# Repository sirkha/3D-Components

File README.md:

3D Components
=============

These are various components and assemblies that I have modeled for use 
in designing 3D printed objects.

I hope you can find some of them as useful as I have.

License
-------
[CC-BY-SA][7]

Attribution
-----------
Thanks to [Adafruit][1] and [Arduino][2] for putting their pcb files on the 
web, which makes the assemblies possible. Also, thanks to [kcswalter][9] for his
excellent 3D models, which I made heavy use of.

Thanks to the following open source software packages:
* [Blender][3]
* [FreeCAD][4]
* [OpenSCAD][5]
* [Inkscape][6]
* [Kicad][8]

[1]: http://adafruit.com "Adafruit Industries"
[2]: http://arduino.cc "Arduino"
[3]: http://blender.org "Blender"
[4]: http://freecad.org "FreeCAD"
[5]: http://openscad.org "OpenSCAD"
[6]: http://inkscape.org "Inkscape"
[7]: https://creativecommons.org/licenses/by-sa/2.0/legalcode "CC-BY-SA"
[8]: http://kicad-pcb.org "Kicad"
[9]: http://smisioto.no-ip.org/elettronica/kicad/kicad-en.htm "Walter Kicad Libs"

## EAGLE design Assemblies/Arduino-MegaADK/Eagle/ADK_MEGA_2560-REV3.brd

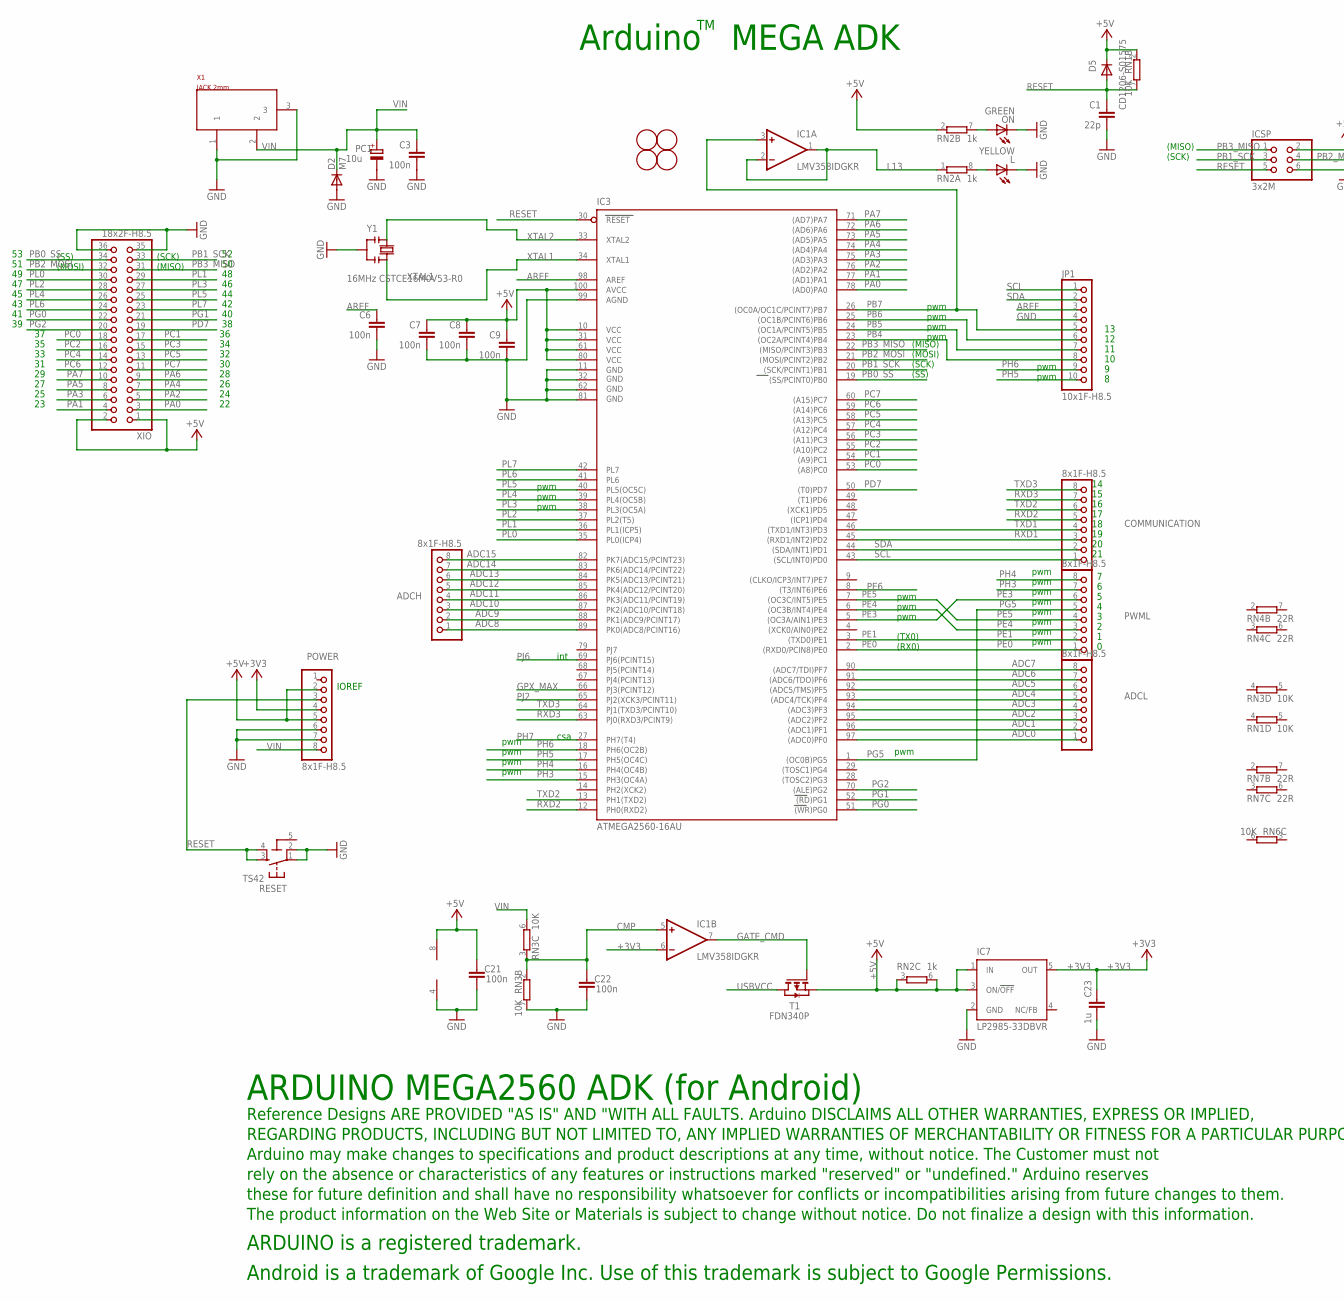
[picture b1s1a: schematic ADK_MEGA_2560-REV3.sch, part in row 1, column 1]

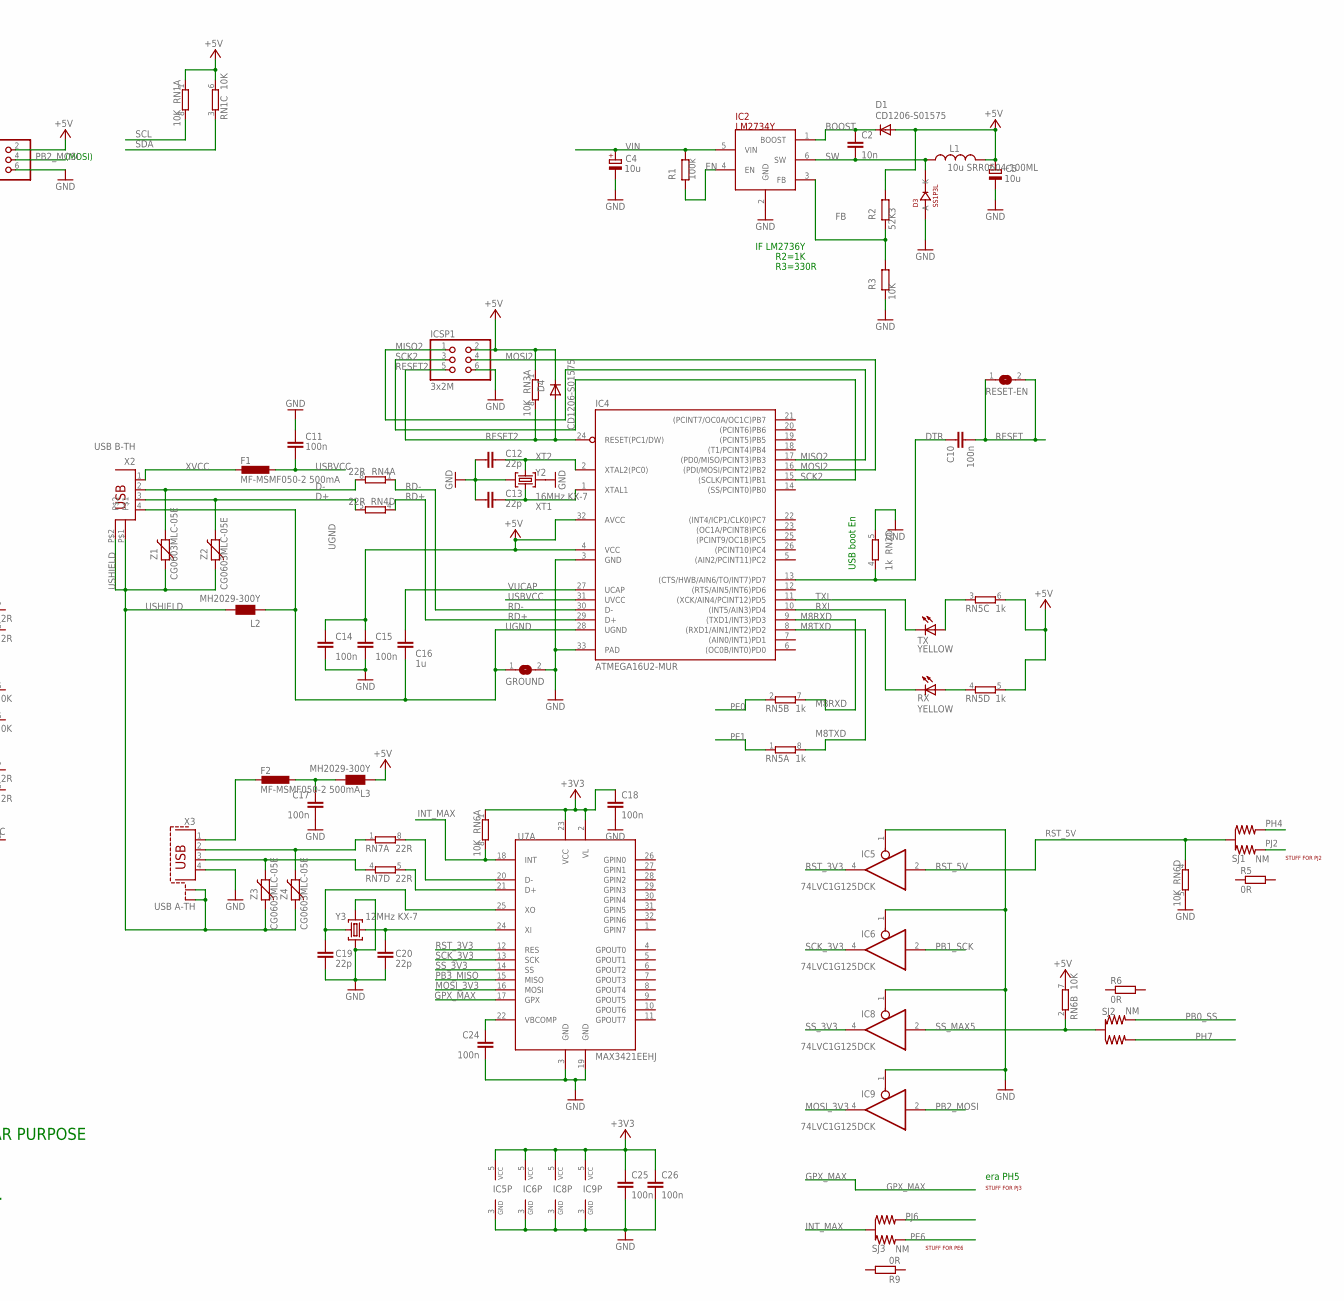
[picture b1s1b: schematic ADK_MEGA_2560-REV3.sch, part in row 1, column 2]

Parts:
ADCH: 8x1F-H8.5; 1X08
ADCL: 8x1F-H8.5; 1X08
C1, C12, C13, C19, C20: 22p; C0603-ROUND
C2: 10n; C0603-ROUND
C3, C6, C7, C8, C9, C10, C11, C14, C15, C17, C18, C21, C22, C24, C25, C26: 100n; C0603-ROUND
C4, C5: 10u; SMC_B
C16, C23: 1u; C0603-ROUND
COMMUNICATION: 8x1F-H8.5; 1X08
D1, D4, D5: CD1206-S01575; MINIMELF
D2: M7; SMB
D3: SS1P3L; DO220AAL
F1, F2: MF-MSMF050-2 500mA; L1812
FID1, FID2, FID3, FID4: FIDUCIALMOUNT; FIDUCIA-MOUNT
GROUND: SJ
IC1: LMV358IDGKR; MSOP08
IC2: LM2734Y; SOT23-6
IC3: ATMEGA2560-16AU; TQFP100
IC4: ATMEGA16U2-MUR; MLF32
IC5, IC6, IC8, IC9: 74LVC1G125DCK; SC70-5
IC7: LP2985-33DBVR; SOT23-DBV
ICSP, ICSP1: 3x2M; 2X03
JP1: 10x1F-H8.5; 1X10
L: YELLOW; CHIP-LED0805
L1: 10u SRR0604-100ML; SRR0604
L2, L3: MH2029-300Y; 0805
ON: GREEN; CHIP-LED0805
PC1: 10u; SMC_B
POWER: 8x1F-H8.5; 1X08
PWML: 8x1F-H8.5; 1X08
R1: 100k; R0603-ROUND
R2: 52K3; R0603-ROUND
R3: 10K; R0603-ROUND
R5, R6, R9: 0R; R0402
RESET: TS42
RESET-EN: SJ
RN1, RN3, RN6: 10K; CAT16
RN2, RN5: 1k; CAY16
RN4, RN7: 22R; CAY16
RX: YELLOW; CHIP-LED0805
SJ1, SJ2, SJ3: NM; J0402
T1: FDN340P; SOT-23
TX: YELLOW; CHIP-LED0805
U7A: MAX3421EEHJ; TQFP32-05
X1: JACK 2mm; POWERSUPPLY_DC-21MM
X2: USB B-TH; PN61729
X3: USB A-TH; PN87520-S
XIO: 18x2F-H8.5; 2X18
Y1: 16MHz CSTCE16M0V53-R0; RESONATOR
Y2: 16MHz KX-7; CRYSTAL-3.2-2.5
Y3: 12MHz KX-7; CRYSTAL-3.2-2.5
Z1, Z2, Z3, Z4: CG0603MLC-05E; CT/CN0603

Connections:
5-GND: RESET.5 (5-GND)
+3V3: C18.1, C23.2, C25.1, C26.1, IC1.6 (-IN), IC5.5 (VCC), IC6.5 (VCC), IC7.5 (OUT), IC8.5 (VCC), IC9.5 (VCC), POWER.4, RN6.1, U7A.2 (VL), U7A.23 (VCC)
+5V: C5.+, C7.1, C8.1, C9.1, C14.1, C15.1, C21.2, D1.A, D4.C, D5.C, IC1.8 (V+), IC3.10 (VCC), IC3.31 (VCC1), IC3.61 (VCC2), IC3.80 (VCC3), IC3.100 (AVCC), IC4.4 (VCC), IC4.32 (AVCC), IC7.1 (IN), IC7.3 (ON/!OFF), ICSP.2, ICSP1.2, L1.P$2 (2), L3.1, POWER.2, POWER.5, R2.1, RN1.1, RN1.2 (1), RN1.6 (2), RN2.2 (1), RN2.3 (1), RN2.6 (2), RN3.1, RN5.5 (2), RN5.6 (2), RN6.7 (2), T1.2 (S), XIO.1, XIO.2
ADC0: ADCL.1, IC3.97 ((ADC0)PF0)
ADC1: ADCL.2, IC3.96 ((ADC1)PF1)
ADC2: ADCL.3, IC3.95 ((ADC2)PF2)
ADC3: ADCL.4, IC3.94 ((ADC3)PF3)
ADC4: ADCL.5, IC3.93 ((ADC4/TCK)PF4)
ADC5: ADCL.6, IC3.92 ((ADC5/TMS)PF5)
ADC6: ADCL.7, IC3.91 ((ADC6/TDO)PF6)
ADC7: ADCL.8, IC3.90 ((ADC7/TDI)PF7)
ADC8: ADCH.1, IC3.89 (PK0(ADC8/PCINT16))
ADC9: ADCH.2, IC3.88 (PK1(ADC9/PCINT17))
ADC10: ADCH.3, IC3.87 (PK2(ADC10/PCINT18))
ADC11: ADCH.4, IC3.86 (PK3(ADC11/PCINT19))
ADC12: ADCH.5, IC3.85 (PK4(ADC12/PCINT20))
ADC13: ADCH.6, IC3.84 (PK5(ADC13/PCINT21))
ADC14: ADCH.7, IC3.83 (PK6(ADC14/PCINT22))
ADC15: ADCH.8, IC3.82 (PK7(ADC15/PCINT23))
AREF: C6.1, IC3.98 (AREF), JP1.3
BOOST: C2.1, D1.C, IC2.1 (BOOST)
CMP: C22.2, IC1.5 (+IN), RN3.2 (1), RN3.3 (1)
D+: RN4.5 (2), X2.3, Z2.2
D-: RN4.8 (2), X2.2, Z1.2
DTR: C10.1, IC4.13 ((CTS/HWB/AIN6/TO/INT7)PD7), RN2.4 (1)
EN: IC2.4 (EN), R1.2
FB: IC2.3 (FB), R2.2, R3.1
GATE_CMD: IC1.7 (OUT), T1.3 (G)
GND: C1.2, C3.2, C4.-, C5.-, C6.2, C7.2, C8.2, C9.2, C11.2, C12.2, C13.2, C14.2, C15.2, C17.2, C18.2, C19.1, C20.1, C21.1, C22.1, C23.1, C24.2, C25.2, C26.2, D2.A, D3.P$2 (A), GROUND.2, IC1.4 (V-), IC2.2 (GND), IC3.11 (GND), IC3.32 (GND1), IC3.62 (GND2), IC3.81 (GND3), IC3.99 (AGND), IC4.3 (GND), IC4.33 (PAD), IC5.1 (OE), IC5.3 (GND), IC6.1 (OE), IC6.3 (GND), IC7.2 (GND), IC8.1 (OE), IC8.3 (GND), IC9.1 (OE), IC9.3 (GND), ICSP.6, ICSP1.6, JP1.4, L.C, ON.C, PC1.-, POWER.6, POWER.7, R3.2, RESET.1, RESET.2, RN2.5 (2), RN3.7 (2), RN6.5 (2), U7A.3 (GND), U7A.19 (GND), X1.1, X1.3, X3.4, XIO.35, XIO.36, Y1.2, Y2.2 (GND), Y2.4 (GND), Y3.2 (GND), Y3.4 (GND)
GPX_MAX: IC3.66 (PJ3(PCINT12)), U7A.17 (GPX)
INT_MAX: RN6.8 (2), SJ3.2 (C), U7A.18 (INT)
L13: IC1.1 (OUT), IC1.2 (-IN), RN2.1
M8RXD: IC4.9 ((TXD1/INT3)PD3), RN5.7 (2)
M8TXD: IC4.8 ((RXD1/AIN1/INT2)PD2), RN5.8 (2)
MISO2: IC4.17 ((PD0/MISO/PCINT3)PB3), ICSP1.1
MOSI2: IC4.16 ((PDI/MOSI/PCINT2)PB2), ICSP1.4
MOSI_3V3: IC9.4 (O), U7A.16 (MOSI)
unnamed: L.A, RN2.8 (2)
unnamed: ON.A, RN2.7 (2)
unnamed: RN7.1, X3.2, Z4.2
unnamed: RN7.4 (1), X3.3, Z3.2
unnamed: RN7.8 (2), U7A.20 (D-)
unnamed: RN7.5 (2), U7A.21 (D+)
unnamed: F2.2, X3.1
unnamed: C20.2, U7A.24 (XI), Y3.1 (C1)
unnamed: C19.2, U7A.25 (XO), Y3.3 (C2)
unnamed: C17.1, F2.1, L3.2
unnamed: C24.1, U7A.22 (VBCOMP)
unnamed: RN5.4 (1), RX.A
unnamed: RN5.3 (1), TX.A
PA0: IC3.78 ((AD0)PA0), XIO.3
PA1: IC3.77 ((AD1)PA1), XIO.4
PA2: IC3.76 ((AD2)PA2), XIO.5
PA3: IC3.75 ((AD3)PA3), XIO.6
PA4: IC3.74 ((AD4)PA4), XIO.7
PA5: IC3.73 ((AD5)PA5), XIO.8
PA6: IC3.72 ((AD6)PA6), XIO.9
PA7: IC3.71 ((AD7)PA7), XIO.10
PB0_SS: IC3.19 ((SS/PCINT0)PB0), SJ2.3 (2), XIO.34
PB1_SCK: IC3.20 ((SCK/PCINT1)PB1), IC6.2 (I), ICSP.3, XIO.33
PB2_MOSI: IC3.21 ((MOSI/PCINT2)PB2), IC9.2 (I), ICSP.4, XIO.32
PB3_MISO: IC3.22 ((MISO/PCINT3)PB3), ICSP.1, U7A.15 (MISO), XIO.31
PB4: IC3.23 ((OC2A/PCINT4)PB4), JP1.8
PB5: IC3.24 ((OC1A/PCINT5)PB5), JP1.7
PB6: IC3.25 ((OC1B/PCINT6)PB6), JP1.6
PB7: IC1.3 (+IN), IC3.26 ((OC0A/OC1C/PCINT7)PB7), JP1.5
PC0: IC3.53 ((A8)PC0), XIO.18
PC1: IC3.54 ((A9)PC1), XIO.17
PC2: IC3.55 ((A10)PC2), XIO.16
PC3: IC3.56 ((A11)PC3), XIO.15
PC4: IC3.57 ((A12)PC4), XIO.14
PC5: IC3.58 ((A13)PC5), XIO.13
PC6: IC3.59 ((A14)PC6), XIO.12
PC7: IC3.60 ((A15)PC7), XIO.11
PD7: IC3.50 ((T0)PD7), XIO.19
PE0: IC3.2 ((RXD0/PCIN8)PE0), PWML.1, RN5.2 (1)
PE1: IC3.3 ((TXD0)PE1), PWML.2, RN5.1
PE3: IC3.5 ((OC3A/AIN1)PE3), PWML.6
PE4: IC3.6 ((OC3B/INT4)PE4), PWML.3
PE5: IC3.7 ((OC3C/INT5)PE5), PWML.4
PE6: IC3.8 ((T3/INT6)PE6), SJ3.3 (2)
PG0: IC3.51 ((WR)PG0), XIO.22
PG1: IC3.52 ((RD)PG1), XIO.21
PG2: IC3.70 ((ALE)PG2), XIO.20
PG5: IC3.1 ((OC0B)PG5), PWML.5
PH3: IC3.15 (PH3(OC4A)), PWML.7
PH4: IC3.16 (PH4(OC4B)), PWML.8, SJ1.1
PH5: IC3.17 (PH5(OC4C)), JP1.10
PH6: IC3.18 (PH6(OC2B)), JP1.9
PH7: IC3.27 (PH7(T4)), SJ2.1
PJ2: IC3.65 (PJ2(XCK3/PCINT11)), SJ1.3 (2)
PJ6: IC3.69 (PJ6(PCINT15)), SJ3.1
PL0: IC3.35 (PL0(ICP4)), XIO.30
PL1: IC3.36 (PL1(ICP5)), XIO.29
PL2: IC3.37 (PL2(T5)), XIO.28
PL3: IC3.38 (PL3(OC5A)), XIO.27
PL4: IC3.39 (PL4(OC5B)), XIO.26
PL5: IC3.40 (PL5(OC5C)), XIO.25
PL6: IC3.41 (PL6), XIO.24
PL7: IC3.42 (PL7), XIO.23
RD+: IC4.29 (D+), RN4.4 (1)
RD-: IC4.30 (D-), RN4.1
RESET: C1.1, C10.2, D5.A, IC3.30 (RESET), ICSP.5, POWER.3, RESET.3, RESET.4, RESET-EN.1, RESET-EN.2, RN1.7 (2)
RESET2: D4.A, IC4.24 (RESET(PC1/DW)), ICSP1.5, RN3.8 (2)
RST_3V3: IC5.4 (O), U7A.12 (RES)
RST_5V: IC5.2 (I), RN6.4 (1), SJ1.2 (C)
RXD1: COMMUNICATION.3, IC3.45 ((RXD1/INT2)PD2)
RXD2: COMMUNICATION.5, IC3.12 (PH0(RXD2))
RXD3: COMMUNICATION.7, IC3.63 (PJ0(RXD3/PCINT9))
RXL: IC4.10 ((INT5/AIN3)PD4), RX.C
SCK2: IC4.15 ((SCLK/PCINT1)PB1), ICSP1.3
SCK_3V3: IC6.4 (O), U7A.13 (SCK)
SCL: COMMUNICATION.1, IC3.43 ((SCL/INT0)PD0), JP1.1, RN1.8 (2)
SDA: COMMUNICATION.2, IC3.44 ((SDA/INT1)PD1), JP1.2, RN1.3 (1)
SS_3V3: IC8.4 (O), U7A.14 (SS)
SS_MAX5: IC8.2 (I), RN6.2 (1), SJ2.2 (C)
SW: C2.2, D3.P$1 (K), IC2.6 (SW), L1.P$1 (1)
TXD1: COMMUNICATION.4, IC3.46 ((TXD1/INT3)PD3)
TXD2: COMMUNICATION.6, IC3.13 (PH1(TXD2))
TXD3: COMMUNICATION.8, IC3.64 (PJ1(TXD3/PCINT10))
TXL: IC4.11 ((XCK/AIN4/PCINT12)PD5), TX.C
UGND: C16.2, GROUND.1, IC4.28 (UGND), L2.1, X2.4
USBVCC: C11.1, F1.1, IC4.31 (UVCC), T1.1 (D)
USHIELD: L2.2, X2.P$1, X2.P$2, X3.S1, X3.S2, Z1.1, Z2.1, Z3.1, Z4.1
VIN: C3.1, C4.+, D2.C, IC2.5 (VIN), PC1.+, POWER.8, R1.1, RN3.6 (2), X1.2
VUCAP: C16.1, IC4.27 (UCAP)
XT1: C13.1, IC4.1 (XTAL1), Y2.1 (C1)
XT2: C12.1, IC4.2 (XTAL2(PC0)), Y2.3 (C2)
XTAL1: IC3.34 (XTAL1), Y1.3
XTAL2: IC3.33 (XTAL2), Y1.1
XVCC: F1.2, X2.1

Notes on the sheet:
Arduino MEGA ADK
(SCK)
(MISO)
(MOSI)
pwm
(TX0)
(RX0)
USB boot En
int
csa
STUFF FOR PJ2
STUFF FOR PJ3
STUFF FOR PE6
(SS)
era PH5
ARDUINO MEGA2560 ADK (for Android)
Reference Designs ARE PROVIDED "AS IS" AND "WITH ALL FAULTS. Arduino DISCLAIMS ALL OTHER WARRANTIES, EXPRESS OR IMPLIED,
Arduino may make changes to specifications and product descriptions at any time, without notice. The Customer must not
REGARDING PRODUCTS, INCLUDING BUT NOT LIMITED TO, ANY IMPLIED WARRANTIES OF MERCHANTABILITY OR FITNESS FOR A PARTICULAR PURPOSE
rely on the absence or characteristics of any features or instructions marked "reserved" or "undefined." Arduino reserves
these for future definition and shall have no responsibility whatsoever for conflicts or incompatibilities arising from future changes to them.
The product information on the Web Site or Materials is subject to change without notice. Do not finalize a design with this information.
ARDUINO is a registered trademark.
Android is a trademark of Google Inc. Use of this trademark is subject to Google Permissions.
IF LM2736Y
R2=1K
R3=330R
IOREF

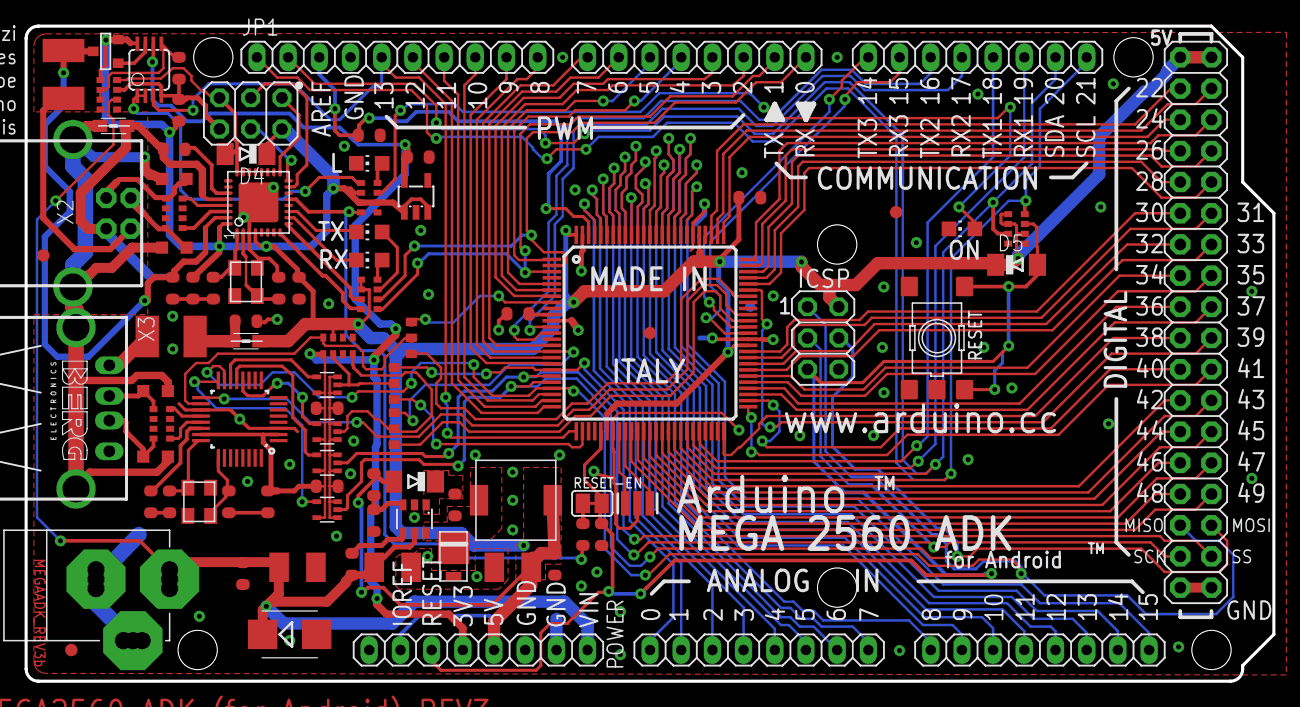
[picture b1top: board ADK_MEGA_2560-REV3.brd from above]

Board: 2 copper layers, 101.6 x 53.3 mm, 94 parts (1 on the bottom side), 130 nets.

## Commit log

2014-10-07 Missed a quote
2014-10-08 Added some missing attribution.
